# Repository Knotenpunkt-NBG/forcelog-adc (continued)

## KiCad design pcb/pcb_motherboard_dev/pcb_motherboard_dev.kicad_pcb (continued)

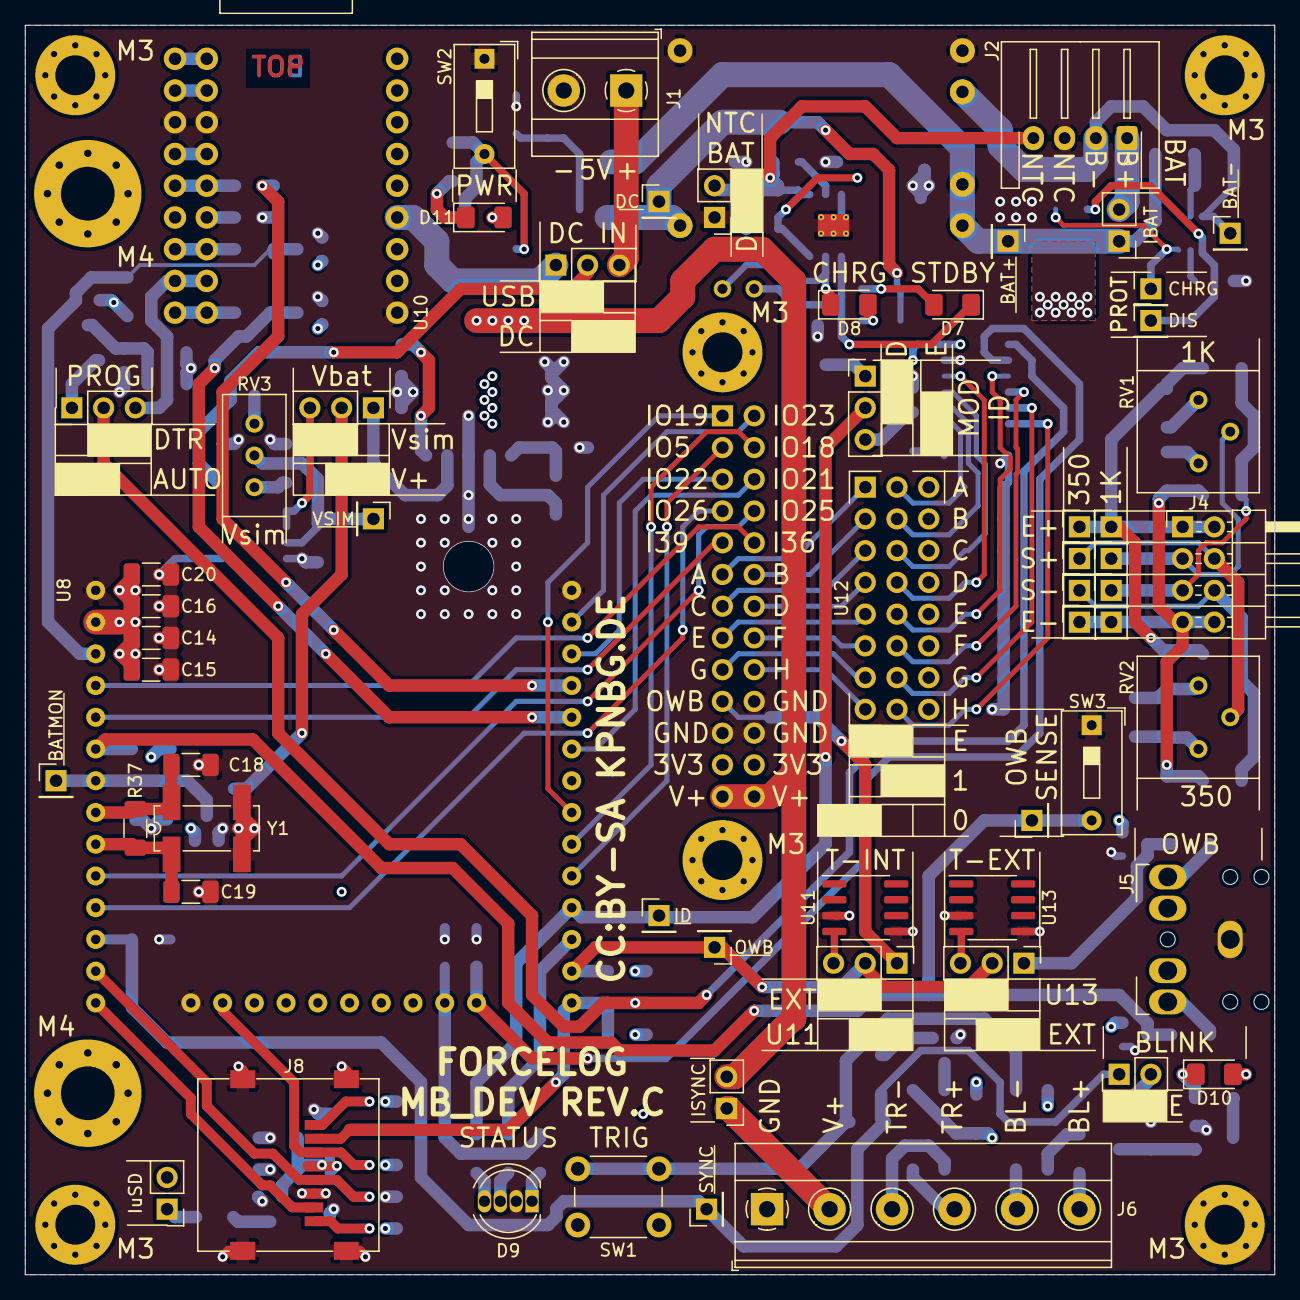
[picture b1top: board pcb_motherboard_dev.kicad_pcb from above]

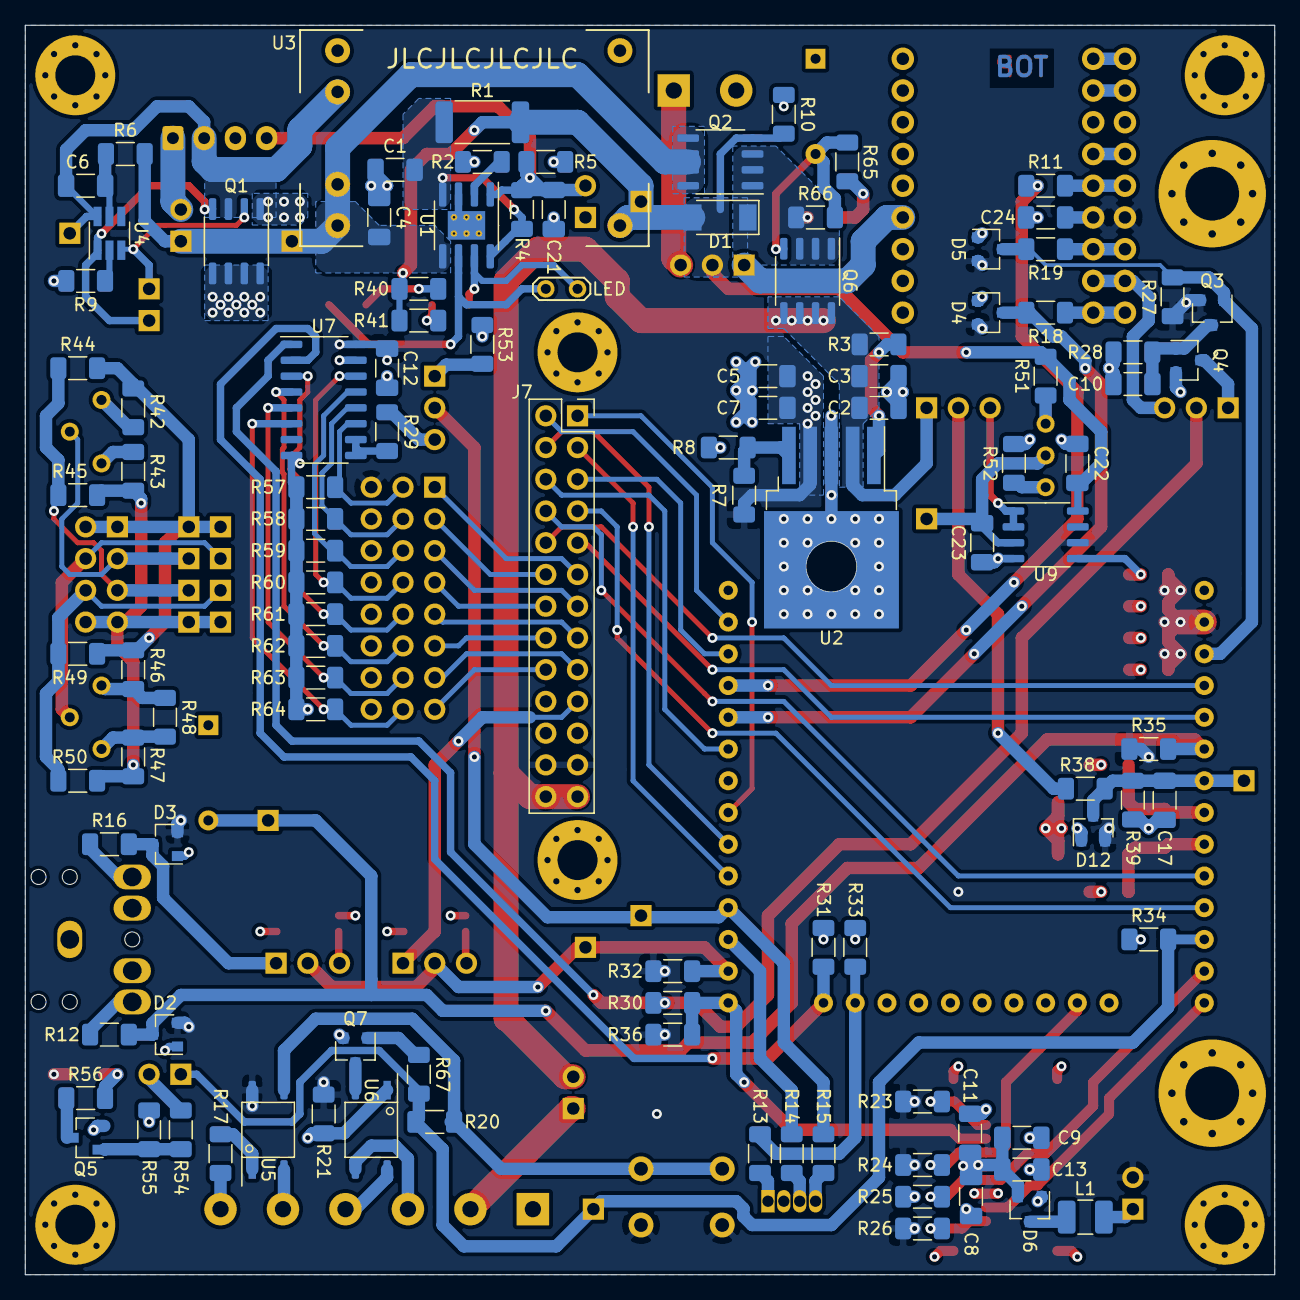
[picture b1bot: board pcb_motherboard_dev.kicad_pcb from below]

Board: 4 copper layers, 100.0 x 100.0 mm, 176 parts (108 on the bottom side), 122 nets.

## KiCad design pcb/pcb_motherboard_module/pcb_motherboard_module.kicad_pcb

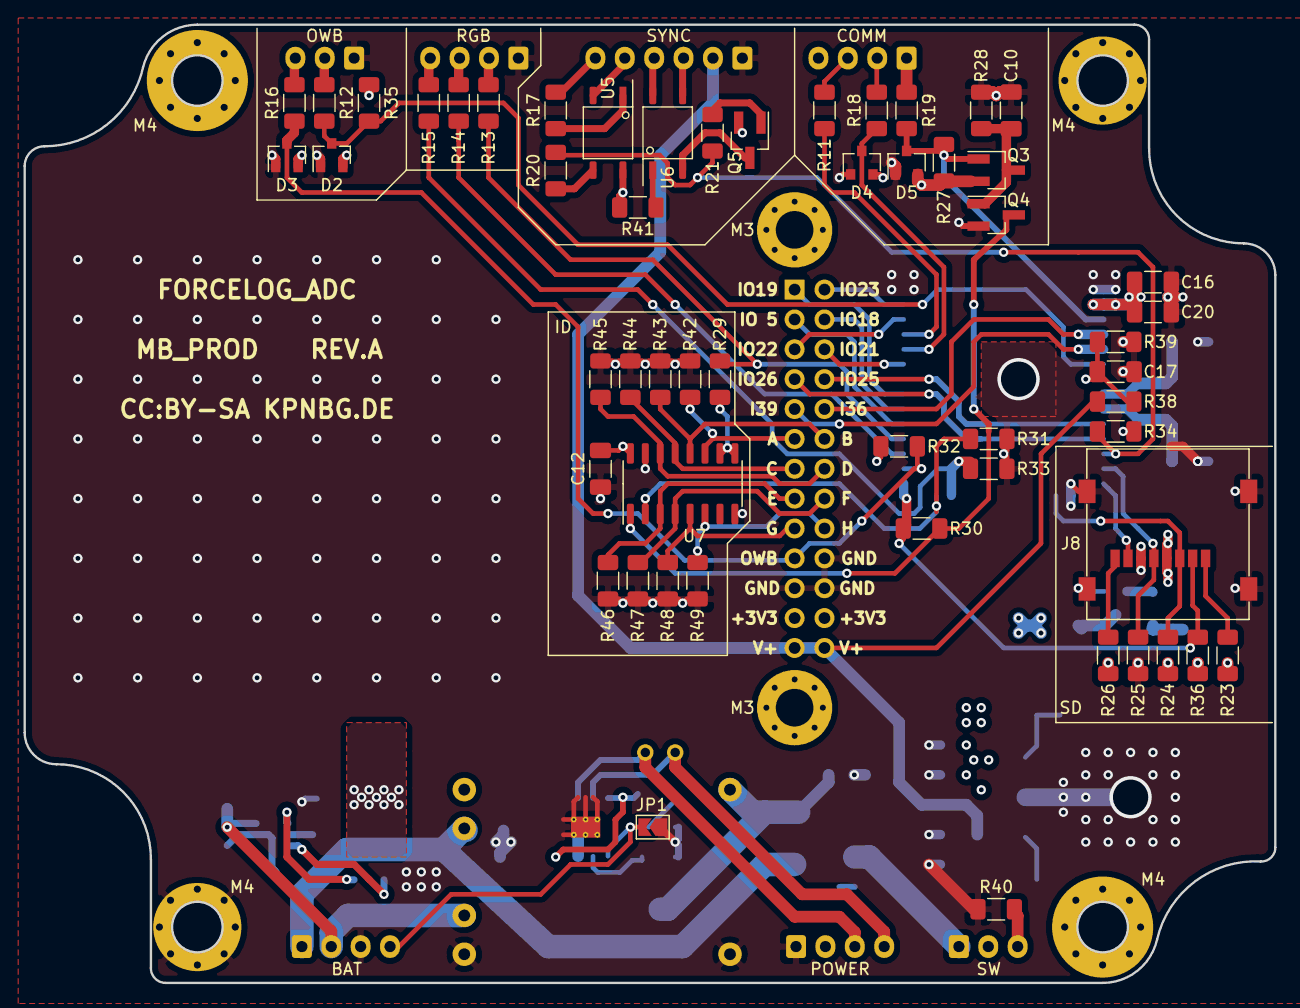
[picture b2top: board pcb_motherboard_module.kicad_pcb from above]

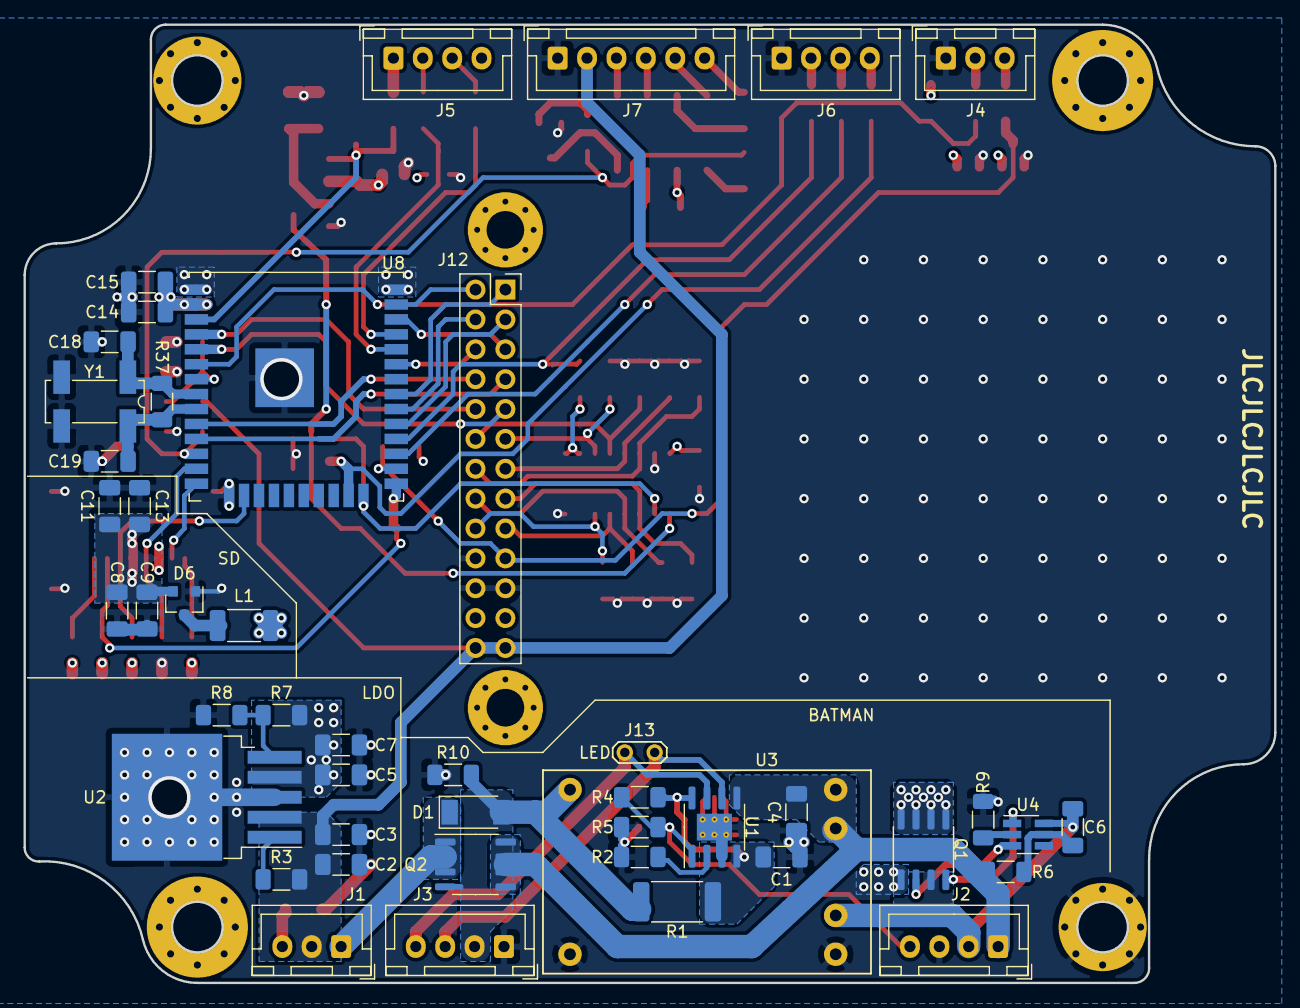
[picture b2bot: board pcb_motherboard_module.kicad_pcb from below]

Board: 4 copper layers, 106.4 x 81.5 mm, 106 parts (46 on the bottom side), 79 nets.

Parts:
C1, C4: 10u; C_1206_3216Metric_Pad1.33x1.80mm_HandSolder
C2, C6, C7, C8, C12, C14, C17: 100n; C_1206_3216Metric_Pad1.33x1.80mm_HandSolder
C3, C5: 22u; C_1206_3216Metric_Pad1.33x1.80mm_HandSolder
C9, C15: 100u; C_1206_3216Metric_Pad1.33x1.80mm_HandSolder
C10: C; C_1206_3216Metric_Pad1.33x1.80mm_HandSolder
C11, C13, C16, C20: 220u; C_1206_3216Metric_Pad1.33x1.80mm_HandSolder
C18, C19: 25p; C_1206_3216Metric_Pad1.33x1.80mm_HandSolder
D1: PMEG3030EP,115; D_SOD-128
D2, D3, D4, D5, D6: BAT54S; SOT-23
H1, H2, H3: MountingHole; MountingHole_4.3mm_M4_Pad_Via
H4: MountingHole_Pad; MountingHole_4.3mm_M4_Pad_Via
H5, H6: MountingHole_Pad; MountingHole_3.2mm_M3_Pad_Via
J1: SW; JST_XH_B3B-XH-A_1x03_P2.50mm_Vertical
J2: BAT; JST_XH_B4B-XH-A_1x04_P2.50mm_Vertical
J3: POWER; JST_XH_B4B-XH-A_1x04_P2.50mm_Vertical
J4: OWB; JST_XH_B3B-XH-A_1x03_P2.50mm_Vertical
J5: COMM; JST_XH_B4B-XH-A_1x04_P2.50mm_Vertical
J6: RGB; JST_XH_B4B-XH-A_1x04_P2.50mm_Vertical
J7: SYNC; JST_XH_B6B-XH-A_1x06_P2.50mm_Vertical
J8: Micro_SD_Card; uSD_Molex_0472192001
J12: Conn_02x13_Odd_Even; PinSocket_2x13_P2.54mm_Vertical
J13: LED; TestPoint_2Pads_Pitch2.54mm_Drill0.8mm
JP1: Jumper_2_Open; SolderJumper-2_P1.3mm_Open_TrianglePad1.0x1.5mm
L1: 47n; L_2010_5025Metric
Q1: DMG9926USD; SO-8_3.9x4.9mm_P1.27mm
Q2: IRF7410TRPBF; SO8_3.8x4.8_SSSGDDDD
Q3: IRLML2244TRPBF; SOT-23_Handsoldering
Q4, Q5: BSS806NE; SOT-23_Handsoldering
R1: 400m; R_2512_6332Metric_Pad1.40x3.35mm_HandSolder
R2: 1k2; R_1206_3216Metric_Pad1.30x1.75mm_HandSolder
R3, R10, R27, R29, R31, R35, R36, R42, R43, R44, R45, R46, R47, R48, R49: 10k; R_1206_3216Metric_Pad1.30x1.75mm_HandSolder
R4, R5, R28, R40: R; R_1206_3216Metric_Pad1.30x1.75mm_HandSolder
R6: 470; R_1206_3216Metric_Pad1.30x1.75mm_HandSolder
R7: 24k; R_1206_3216Metric_Pad1.30x1.75mm_HandSolder
R8: 5k6; R_1206_3216Metric_Pad1.30x1.75mm_HandSolder
R9, R13, R14, R15, R20, R21, R30, R32: 1k; R_1206_3216Metric_Pad1.30x1.75mm_HandSolder
R11, R41: 100; R_1206_3216Metric_Pad1.30x1.75mm_HandSolder
R12, R16, R18, R19: 10; R_1206_3216Metric_Pad1.30x1.75mm_HandSolder
R17: 210; R_1206_3216Metric_Pad1.30x1.75mm_HandSolder
R23, R24, R25, R26, R34: 22k; R_1206_3216Metric_Pad1.30x1.75mm_HandSolder
R33: 100k; R_1206_3216Metric_Pad1.30x1.75mm_HandSolder
R37: 5Meg; R_1206_3216Metric_Pad1.30x1.75mm_HandSolder
R38: 3k; R_1206_3216Metric_Pad1.30x1.75mm_HandSolder
R39: 7k5; R_1206_3216Metric_Pad1.30x1.75mm_HandSolder
U1: TP4056; SOIC-8-1EP_3.9x4.9mm_P1.27mm_EP2.29x3mm_ThermalVias
U2: LP38501; TO-263-5_TabPin6
U3: TP4056withprotect; TP4056_module_prot
U4: NT1713C; SOT-23-6_Handsoldering
U5, U6: EL357NC; EL357N
U7: 74165; SO-16_3.9x9.9mm_P1.27mm
U8: ESP32-WROOM-32; ESP32-WROOM-32U
Y1: 32.768 kHz; Crystal_SMD_SeikoEpson_MC306-4Pin_8.0x3.2mm_HandSoldering

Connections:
+3V3: C5.1, C7.1, C12.1, C14.1, C15.1, C16.1, C20.1, D2.2, D3.2, D4.2, D5.2, J5.4, J12.23, J12.24, L1.2, Q3.2, R7.1, R23.1, R24.1, R26.1, R27.1, R32.1, R35.1, R36.2, R41.2, U2.4, U5.4, U7.16, U8.2
/CONTROLLER/A: J12.11, R42.2, U7.11
/CONTROLLER/B: J12.12, R43.2, U7.12
/CONTROLLER/BLUE: R13.2, R29.2, U8.28
/CONTROLLER/C: J12.13, R44.2, U7.13
/CONTROLLER/CLK: R31.2, U7.2, U8.24
/CONTROLLER/D: J12.14, R45.2, U7.14
/CONTROLLER/DQ: D3.3, J12.19, R16.2, R32.2, U8.26
/CONTROLLER/DTR: Q4.3, R30.2, U7.1
/CONTROLLER/E: J12.15, R46.2, U7.3
/CONTROLLER/F: J12.16, R47.2, U7.4
/CONTROLLER/G: J12.17, R48.2, U7.5
/CONTROLLER/GREEN: R14.2, U8.27
/CONTROLLER/H: J12.18, R49.2, U7.6
/CONTROLLER/HCLK: J8.5, R25.2, U8.13
/CONTROLLER/HMISO: J8.7, U8.14
/CONTROLLER/HMOSI: J8.3, R24.2, U8.16
/CONTROLLER/HMSS: J8.2, R30.1, R36.1, U8.25
/CONTROLLER/IO_5|V~CS: J12.3, U8.29
/CONTROLLER/IO_18|VCLK: J12.4, U8.30
/CONTROLLER/IO_19|VMISO: J12.1, U8.31
/CONTROLLER/IO_21|SDA: J12.6, U8.33
/CONTROLLER/IO_22|SCL: J12.5, U8.36
/CONTROLLER/IO_23|VMOSI: J12.2, U8.37
/CONTROLLER/IO_25|DAC1: J12.8, U8.10
/CONTROLLER/IO_26|DAC2: J12.7, U8.11
/CONTROLLER/I_36|ADC1_0: J12.10, U8.4
/CONTROLLER/I_39|ADC1_3: J12.9, U8.5
/CONTROLLER/OWB_SENSE: D2.3, R12.2, R35.2, U8.6
/CONTROLLER/RED: R15.2, R33.2, U8.23
/CONTROLLER/RTS: D5.3, Q3.1, R19.2, R27.2, U8.3
/CONTROLLER/RXD: D4.3, R18.2, U8.34
/CONTROLLER/SYNC: R20.1, R21.2, R34.2, U8.12
/CONTROLLER/TXD: R11.2, U8.35
/POWER/BAT+: C4.1, J2.1, Q2.1, R6.2, U1.5, U3.5, U3.6
/POWER/BAT-: C6.2, J2.2, Q1.3, U3.4, U4.6
/POWER/DC_IN: D1.2, J3.2, Q2.2, R1.1, R10.1, U3.1
/POWER/SW: D1.1, J1.1, Q2.3
/POWER/TEMP: J2.4, JP1.2, R4.2, R5.1, U1.1
/POWER/~LED_CHRG: J3.4, J13.1, U1.7
/POWER/~LED_STBY: J3.3, J13.2, U1.6
GND: C1.2, C2.2, C3.2, C4.2, C5.2, C7.2, C8.2, C9.2, C10.2, C11.2, C12.2, C13.2, C14.2, C15.2, C16.2, C17.2, C18.1, C19.2, C20.2, D2.1, D3.1, D4.1, D5.1, D6.1, H4.1, J2.3, J3.1, J4.1, J6.1, J7.1, J8.6, J8.9, J12.20, J12.21, J12.22, JP1.1, Q1.1, Q4.2, Q5.2, R2.2, R5.2, R8.2, R9.2, R10.2, R25.1, R28.2, R31.1, R33.1, R34.1, R39.2, R40.2, R42.1, R43.1, R44.1, R45.1, R46.1, R47.1, R48.1, R49.1, U1.3, U1.9, U2.3, U2.6, U3.2, U3.3, U7.8, U7.15, U8.1, U8.15, U8.38, U8.39, Y1.2, Y1.3
unnamed: C1.1, R1.2, R4.1, U1.4, U1.8
unnamed: C6.1, R6.1, U4.5
unnamed: C10.1, Q3.3, Q4.1, R28.1
unnamed: C8.1, C9.1, C11.1, C13.1, D6.2, J8.4
unnamed: C17.1, R38.2, R39.1, U8.7
unnamed: C18.2, R37.2, U8.8, Y1.1
unnamed: C19.1, R37.1, U8.9, Y1.4
unnamed: D6.3, L1.1
unnamed: J1.3, R40.1
unnamed: J4.2, R12.1
unnamed: J4.3, R16.1
unnamed: J5.1, R19.1
unnamed: J5.2, R18.1
unnamed: J5.3, R11.1
unnamed: J6.2, R13.1
unnamed: J6.3, R14.1
unnamed: J6.4, R15.1
unnamed: J7.3, U6.3
unnamed: J7.4, U6.4
unnamed: J7.5, U5.2
unnamed: J7.6, R17.1
unnamed: J8.1, R23.2
unnamed: J8.8, R26.2
unnamed: Q1.2, U4.3
unnamed: Q1.4, U4.1
unnamed: Q1.5, Q1.6, Q1.7, Q1.8
unnamed: Q5.1, R21.1
unnamed: Q5.3, U6.2
unnamed: R2.1, U1.2
unnamed: R3.1, U2.1
unnamed: R7.2, R8.1, U2.5
unnamed: R9.1, U4.2
unnamed: R17.2, U5.1
unnamed: R20.2, U5.3
unnamed: R29.1, U7.9, U7.10
unnamed: R41.1, U6.1
VDD: C2.1, C3.1, J1.2, J7.2, J12.25, J12.26, R3.2, R38.1, U2.2

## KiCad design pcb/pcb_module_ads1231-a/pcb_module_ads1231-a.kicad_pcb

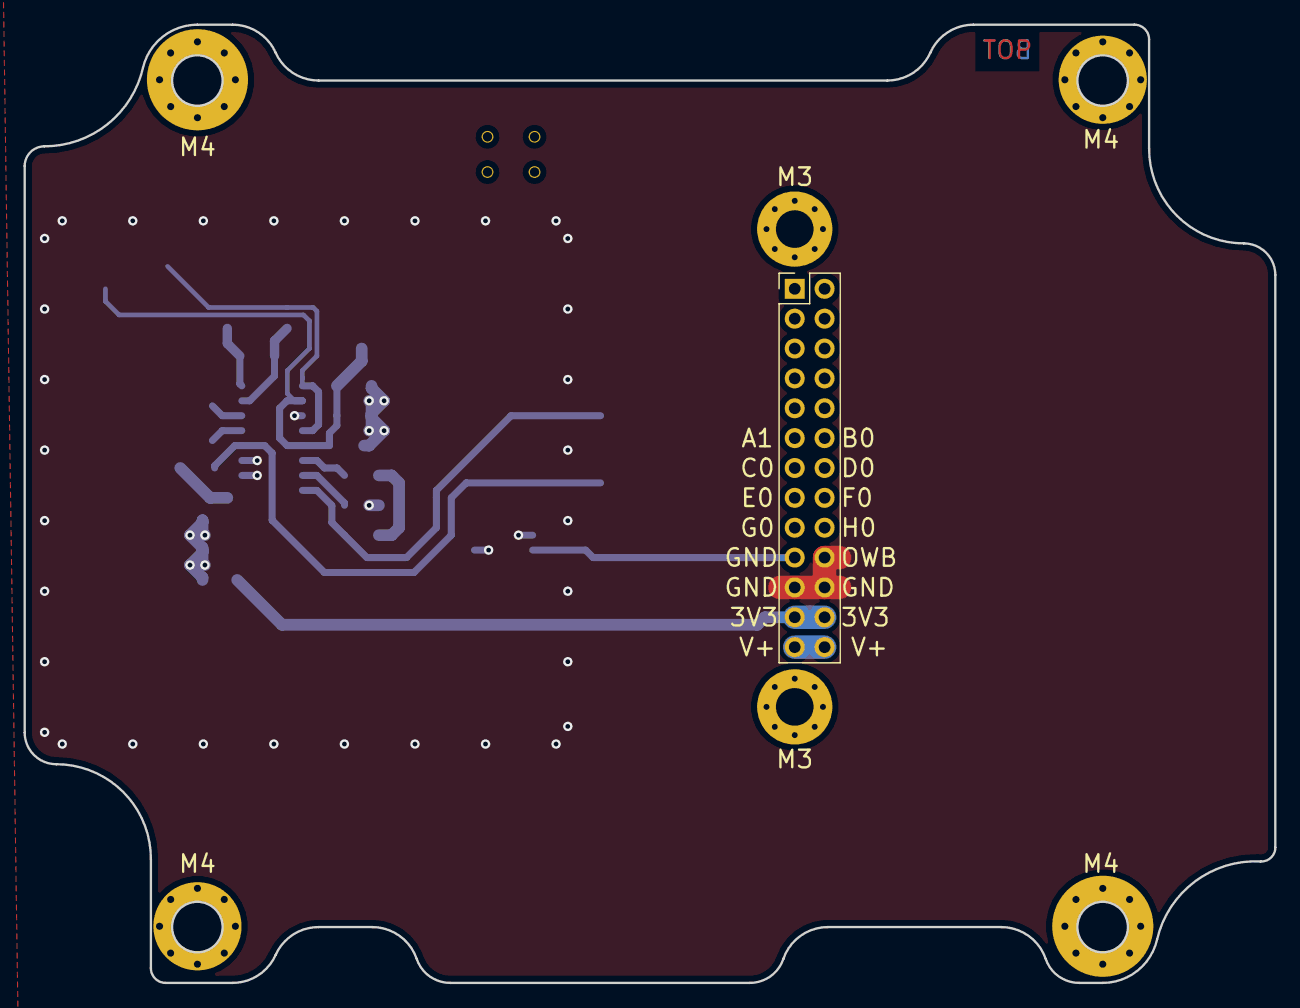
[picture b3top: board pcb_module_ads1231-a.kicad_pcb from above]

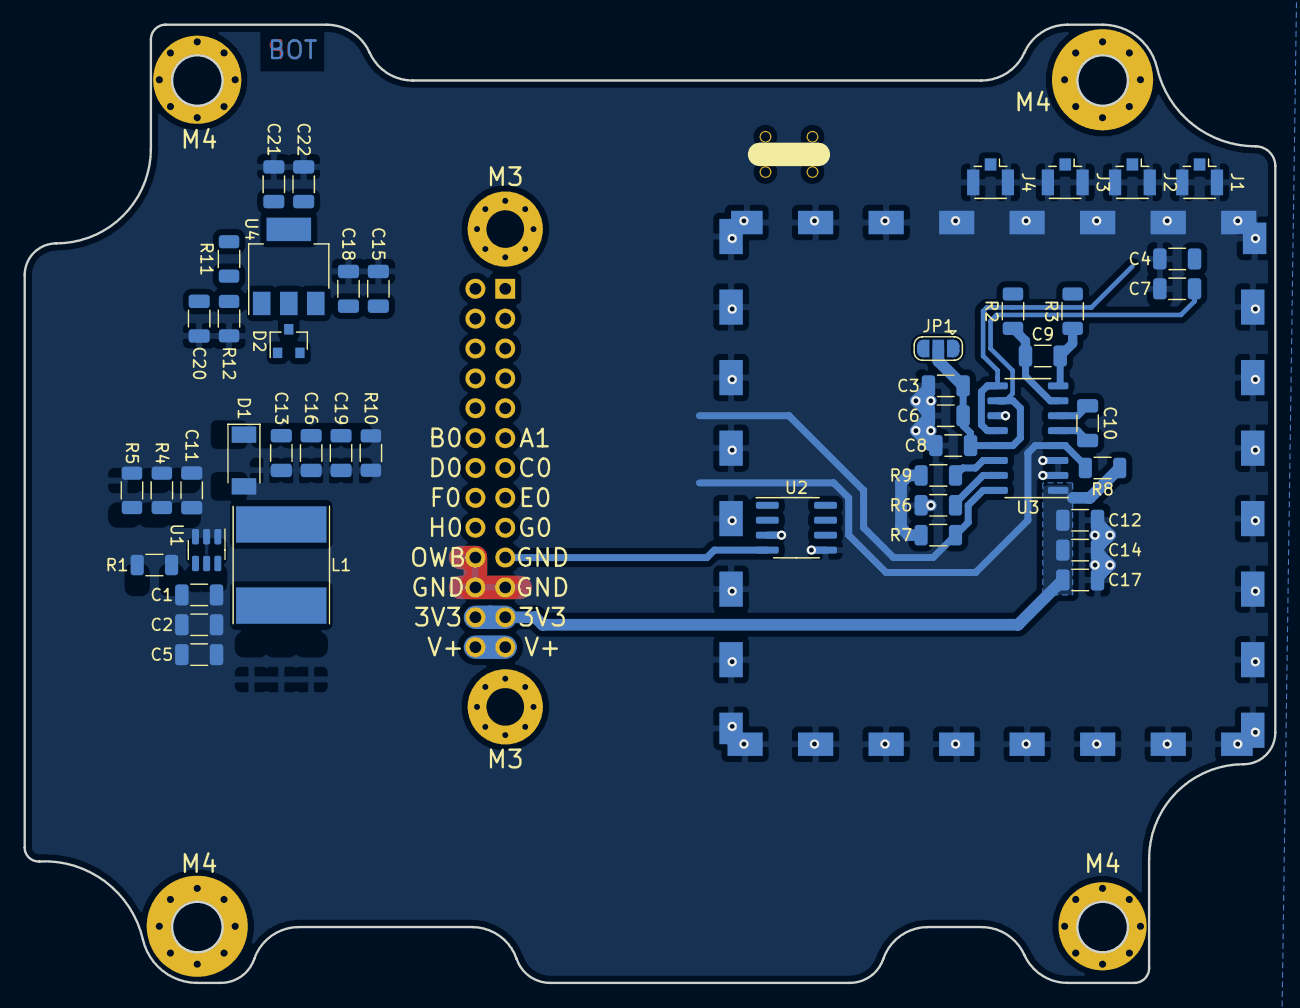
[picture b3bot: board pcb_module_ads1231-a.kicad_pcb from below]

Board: 2 copper layers, 106.4 x 81.5 mm, 55 parts (48 on the bottom side), 22 nets.

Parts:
C1, C4, C8, C9, C10, C12, C13, C18, C21: 100n; C_1206_3216Metric
C2, C6, C7, C14, C15, C16, C22: 10u; C_1206_3216Metric
C3, C17: 47u; C_1206_3216Metric
C5, C19: 100u; C_1206_3216Metric
C11: 330p; C_1206_3216Metric
C20: 10n; C_1206_3216Metric
D1: PMEG3030EP,115; D_SOD-128
D2: D_Dual_Series_AKC; SOT-23
H1, H2: MountingHole_Pad; MountingHole_3.2mm_M3_Pad_Via
H3: MountingHole; cableclamp_4x1.13_coax_bundled
H4, H5, H6, H7: MountingHole_Pad; MountingHole_4.3mm_M4_Pad_Via
J1, J2, J3, J4: Conn_Coaxial; U.FL_Hirose_U.FL-R-SMT-1_Vertical
J5: RFShield_TwoPieces; Shield_TE2118726-2
J7: Conn_02x13_Odd_Even; PinHeader_2x13_P2.54mm_Vertical
JP1: SolderJumper_3_Open; SolderJumper-3_P1.3mm_Open_RoundedPad1.0x1.5mm
L1: 10u; L_Taiyo-Yuden_NR-80xx_HandSoldering
R1: 51k; R_1206_3216Metric
R2, R3: 100; R_1206_3216Metric
R4: 130k; R_1206_3216Metric
R5: 9k1; R_1206_3216Metric
R6, R7, R8, R9: 10k; R_1206_3216Metric
R10, R12: 1k; R_1206_3216Metric
R11: 330; R_1206_3216Metric
U1: MT3608; SOT-23-6
U2: DS18B20Z; SOIC-8_3.9x4.9mm_P1.27mm
U3: ads1231; SO-16_3.9x9.9mm_P1.27mm
U4: LM317_SOT-223; SOT-223-3_TabPin2

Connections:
+3V3: C12.1, C14.1, C17.1, J7.23, J7.24, JP1.3, R7.1, R8.1, R9.1, U3.1
+5VA: C21.1, C22.1, D2.3, JP1.1, R11.1, U4.2
+9V: C11.1, C13.1, C15.1, C16.1, C18.1, C19.1, D1.1, D2.2, R4.1, R10.1, U4.3
/DOUT: J7.1, R7.2, U3.16
/DQ: J7.19, U2.4
/E+: C3.1, C4.1, C6.1, C7.1, C8.1, J1.1, JP1.2, U3.10, U3.13
/E-: J2.1, U3.9, U3.12
/EN: R1.2, U1.4
/PDWN: J7.8, R9.2, U3.14
/S+: J4.1, R2.2
/S-: J3.1, R3.2
/SCLK: J7.4, R6.2, U3.15
/SPEED: J7.6, R8.2, U3.4
GND: C1.2, C2.2, C3.2, C4.2, C5.2, C6.2, C7.2, C8.2, C12.2, C13.2, C14.2, C15.2, C16.2, C17.2, C18.2, C19.2, C20.2, C21.2, C22.2, J1.2, J2.2, J3.2, J4.2, J5.1, J7.20, J7.21, J7.22, R5.2, R6.1, R10.2, R12.2, U1.2, U2.3, U2.5, U3.2, U3.3, U3.11
unnamed: C9.1, R2.1, U3.7
unnamed: C9.2, R3.1, U3.8
unnamed: C10.1, U3.5
unnamed: C10.2, U3.6
unnamed: C11.2, R4.2, R5.1, U1.3
unnamed: C20.1, D2.1, R11.2, R12.1, U4.1
unnamed: D1.2, L1.2, U1.1
V+: C1.1, C2.1, C5.1, J7.25, J7.26, L1.1, R1.1, U1.5

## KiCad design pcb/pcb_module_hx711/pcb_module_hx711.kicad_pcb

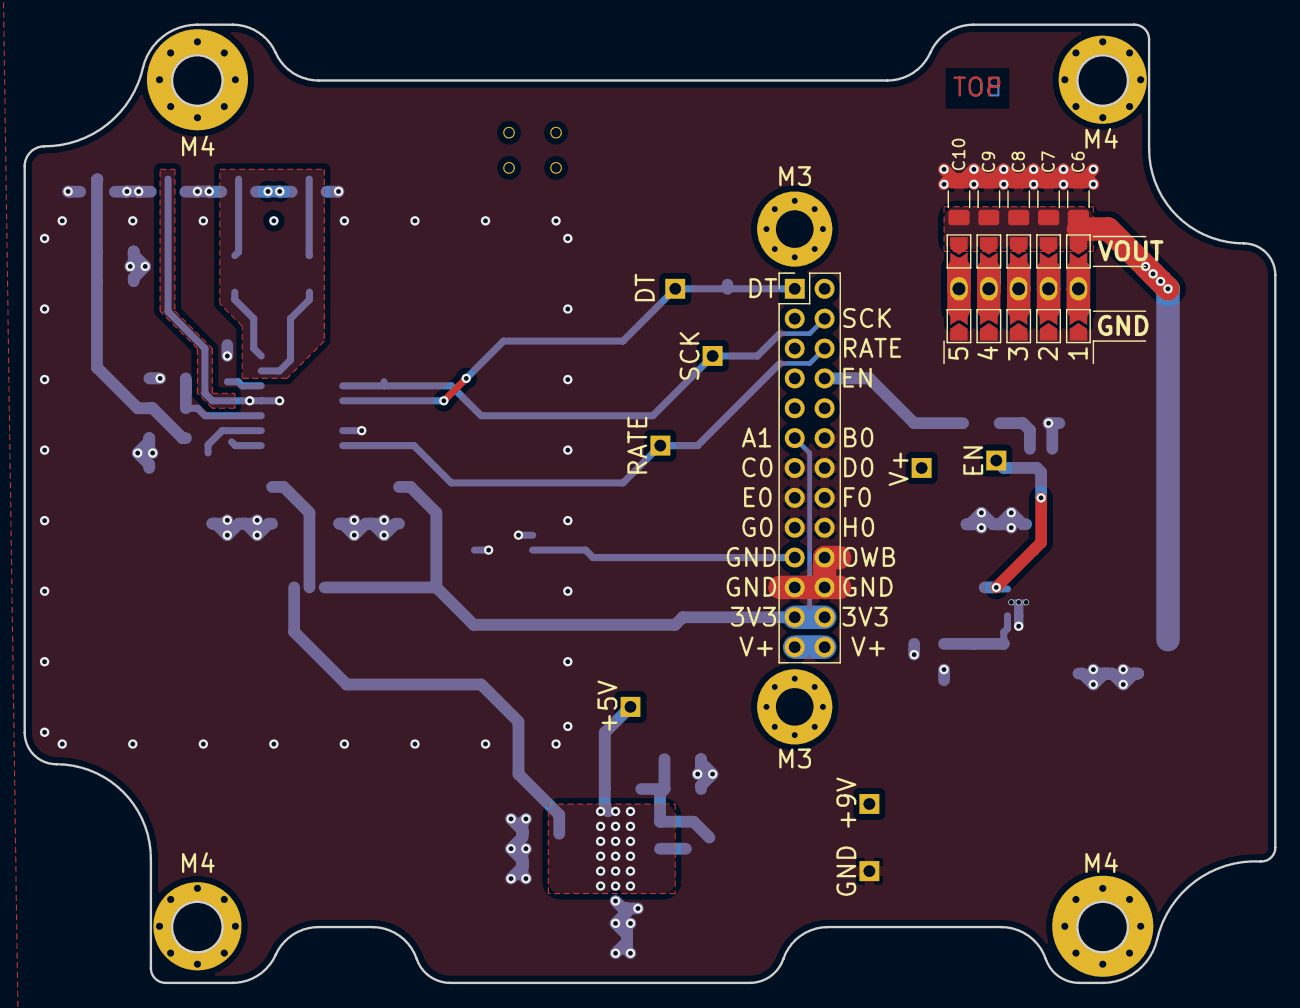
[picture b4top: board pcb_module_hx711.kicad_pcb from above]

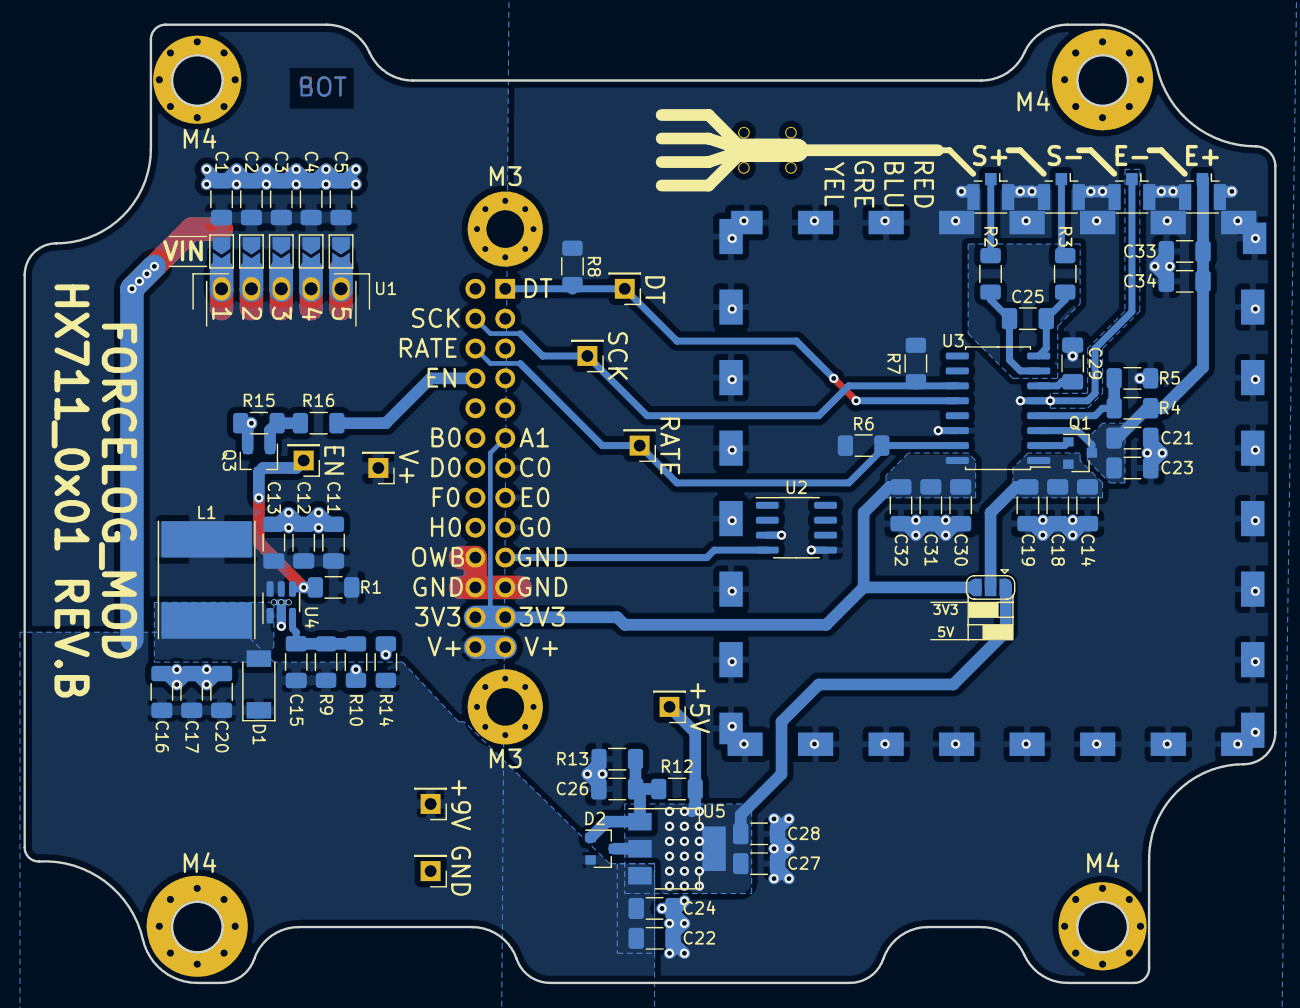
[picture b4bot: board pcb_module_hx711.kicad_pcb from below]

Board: 2 copper layers, 106.4 x 81.5 mm, 96 parts (74 on the bottom side), 29 nets.

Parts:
C1, C2, C3, C4, C5, C6, C7, C8, C9, C10, C12, C17, C18, C22, C23, C26, C28, C31, C34: 10u; C_1206_3216Metric_Pad1.33x1.80mm_HandSolder
C11, C16: 100u; C_1206_3216Metric_Pad1.33x1.80mm_HandSolder
C13, C19, C20, C21, C24, C25, C27, C29, C30, C33: 100n; C_1206_3216Metric_Pad1.33x1.80mm_HandSolder
C14, C32: 47u; C_1206_3216Metric_Pad1.33x1.80mm_HandSolder
C15: 330p; C_1206_3216Metric_Pad1.33x1.80mm_HandSolder
D1: D_Schottky; D_SOD-128
D2: BAT54S; SOT-23
H1, H2: MountingHole_Pad; MountingHole_3.2mm_M3_Pad_Via
H3: MountingHole; cableclamp_4x1.13_coax_bundled
H4, H5, H6, H7: MountingHole_Pad; MountingHole_4.3mm_M4_Pad_Via
J1: E+; U.FL_Hirose_U.FL-R-SMT-1_Vertical
J2: E-; U.FL_Hirose_U.FL-R-SMT-1_Vertical
J3: S+; U.FL_Hirose_U.FL-R-SMT-1_Vertical
J4: S-; U.FL_Hirose_U.FL-R-SMT-1_Vertical
J5: RFShield_TwoPieces; Shield_TE2118726-2
J7: Conn_02x13_Odd_Even; PinHeader_2x13_P2.54mm_Vertical
JP1, JP2, JP3, JP4, JP5, JP6, JP7, JP8, JP9, JP10, JP11, JP12, JP13, JP14, JP15: Jumper_2_Open; SolderJumper-2_P1.3mm_Open_TrianglePad1.0x1.5mm
JP16: Jumper_3_Open; SolderJumper-3_P1.3mm_Open_RoundedPad1.0x1.5mm
L1: 10; L_Taiyo-Yuden_NR-80xx_HandSoldering
Q1: MMBT4403L; SOT-23
Q3: BSS806NE; SOT-23
R1: 51k; R_1206_3216Metric_Pad1.30x1.75mm_HandSolder
R2, R3: 100; R_1206_3216Metric_Pad1.30x1.75mm_HandSolder
R4: 20k; R_1206_3216Metric_Pad1.30x1.75mm_HandSolder
R5: 7k15; R_1206_3216Metric_Pad1.30x1.75mm_HandSolder
R6, R7, R8, R15: 10k; R_1206_3216Metric_Pad1.30x1.75mm_HandSolder
R9: 130k; R_1206_3216Metric_Pad1.30x1.75mm_HandSolder
R10: 9k1; R_1206_3216Metric_Pad1.30x1.75mm_HandSolder
R12: 330; R_1206_3216Metric_Pad1.30x1.75mm_HandSolder
R13, R14: 1k; R_1206_3216Metric_Pad1.30x1.75mm_HandSolder
R16: 220; R_1206_3216Metric_Pad1.30x1.75mm_HandSolder
TP1, TP2: GND; PinHeader_1x01_P2.54mm_Vertical
TP3: SCK; PinHeader_1x01_P2.54mm_Vertical
TP4: DT; PinHeader_1x01_P2.54mm_Vertical
TP5: RATE; PinHeader_1x01_P2.54mm_Vertical
TP6: +9V; PinHeader_1x01_P2.54mm_Vertical
TP7: +5V; PinHeader_1x01_P2.54mm_Vertical
TP8: TP; PinHeader_1x01_P2.54mm_Vertical
U1: BOOST MODULE; boost_generic_var
U2: DS18B20Z; SOIC-8_3.9x4.9mm_P1.27mm
U3: HX711; SO-16_5.3x10.2mm_P1.27mm
U4: MT3608; SOT-23-6
U5: LM317_SOT-223; SOT-223-3_TabPin2

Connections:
+3V3: C30.1, C31.1, C32.1, J7.11, J7.23, J7.24, JP16.3, U3.16
+5VA: C27.1, C28.1, D2.3, JP16.1, R12.1, TP7.1, U5.2
+9V: C6.2, C7.2, C8.2, C9.2, C10.2, C15.1, C16.1, C17.1, C20.1, C22.1, C24.1, D1.1, D2.2, JP11.1, JP12.1, JP13.1, JP14.1, JP15.1, R9.1, R14.1, TP6.1, U5.3
/BOOST_PIN1: JP1.2, JP6.2, JP11.2, U1.1
/BOOST_PIN2: JP2.2, JP7.2, JP12.2, U1.2
/BOOST_PIN3: JP3.2, JP8.2, JP13.2, U1.3
/BOOST_PIN4: JP4.2, JP9.2, JP14.2, U1.4
/BOOST_PIN5: JP5.2, JP10.2, JP15.2, U1.5
/DQ: J7.19, U2.4
/DT: J7.1, R8.2, TP4.1, U3.12
/EN: Q3.3, R1.2, TP8.1, U4.4
/RATE: J7.6, R6.2, TP5.1, U3.15
/SCK: J7.4, R7.2, TP3.1, U3.11
GND: C1.1, C2.1, C3.1, C4.1, C5.1, C6.1, C7.1, C8.1, C9.1, C10.1, C11.2, C12.2, C13.2, C14.2, C16.2, C17.2, C18.2, C19.2, C20.2, C21.2, C22.2, C23.2, C24.2, C26.2, C27.2, C28.2, C29.2, C30.2, C31.2, C32.2, C33.2, C34.2, J1.2, J2.2, J3.2, J4.2, J5.1, J7.12, J7.13, J7.14, J7.15, J7.16, J7.17, J7.18, J7.20, J7.21, J7.22, JP6.1, JP7.1, JP8.1, JP9.1, JP10.1, Q3.2, R5.2, R6.1, R7.1, R8.1, R10.2, R13.2, R14.2, R15.2, TP2.1, U2.3, U2.5, U3.5, U3.14, U4.2
unnamed: C14.1, C18.1, C19.1, JP16.2, Q1.2, U3.1
unnamed: C15.2, R9.2, R10.1, U4.3
unnamed: C21.1, C23.1, C33.1, C34.1, J1.1, Q1.3, R4.1, U3.3
unnamed: C25.1, R2.2, U3.7
unnamed: C25.2, R3.2, U3.8
unnamed: C26.1, D2.1, R12.2, R13.1, U5.1
unnamed: C29.1, U3.6
unnamed: D1.2, L1.2, U4.1
unnamed: J3.1, R3.1
unnamed: J4.1, R2.1
unnamed: J7.8, R16.2
unnamed: Q1.1, U3.2
unnamed: Q3.1, R15.1, R16.1
unnamed: R4.2, R5.1, U3.4
V+: C1.2, C2.2, C3.2, C4.2, C5.2, C11.1, C12.1, C13.1, J7.25, J7.26, JP1.1, JP2.1, JP3.1, JP4.1, JP5.1, L1.1, R1.1, TP1.1, U4.5, U4.6

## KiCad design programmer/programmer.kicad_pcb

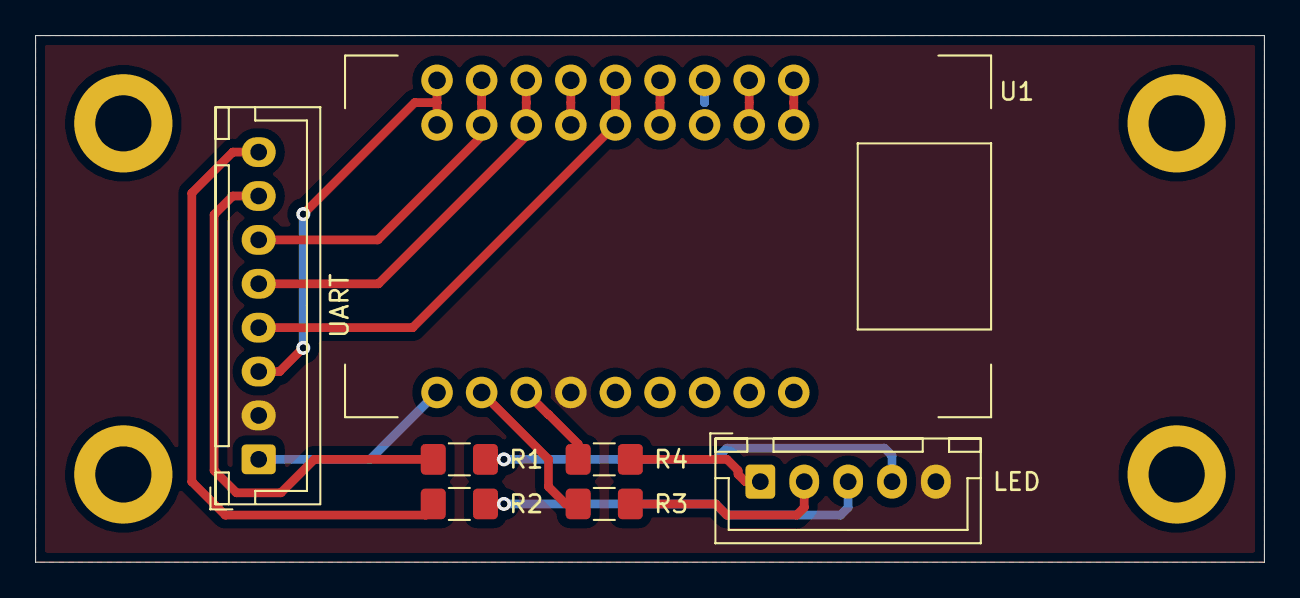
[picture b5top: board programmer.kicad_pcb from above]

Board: 2 copper layers, 70.0 x 30.0 mm, 11 parts (0 on the bottom side), 14 nets.

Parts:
P1: UART; JST_XH_B8B-XH-A_1x08_P2.50mm_Vertical
P2: LED; JST_XH_B5B-XH-A_1x05_P2.50mm_Vertical
P3, P4, P5, P6: CONN_01X01; MountingHole_3.2mm_M3_DIN965_Pad
R1, R2, R3, R4: 150; R_1206_3216Metric_Pad1.42x1.75mm_HandSolder
U1: FT232breakout; ft232rl_breakout_combined

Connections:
+5V: P1.2, P2.5, U1.15
/CHRGLED: P1.7, R1.2
/DTR: P1.6, U1.8
/FINLED: P1.8, R2.2
/RTS: P1.5, U1.7
/RXD: P1.4, U1.5
/RXLED: R4.2, U1.16
/TXD: P1.3, U1.9
/TXLED: R3.2, U1.17
GND: P1.1, U1.3, U1.18
unnamed: P2.1, R4.1
unnamed: P2.2, R3.1
unnamed: P2.3, R2.1
unnamed: P2.4, R1.1

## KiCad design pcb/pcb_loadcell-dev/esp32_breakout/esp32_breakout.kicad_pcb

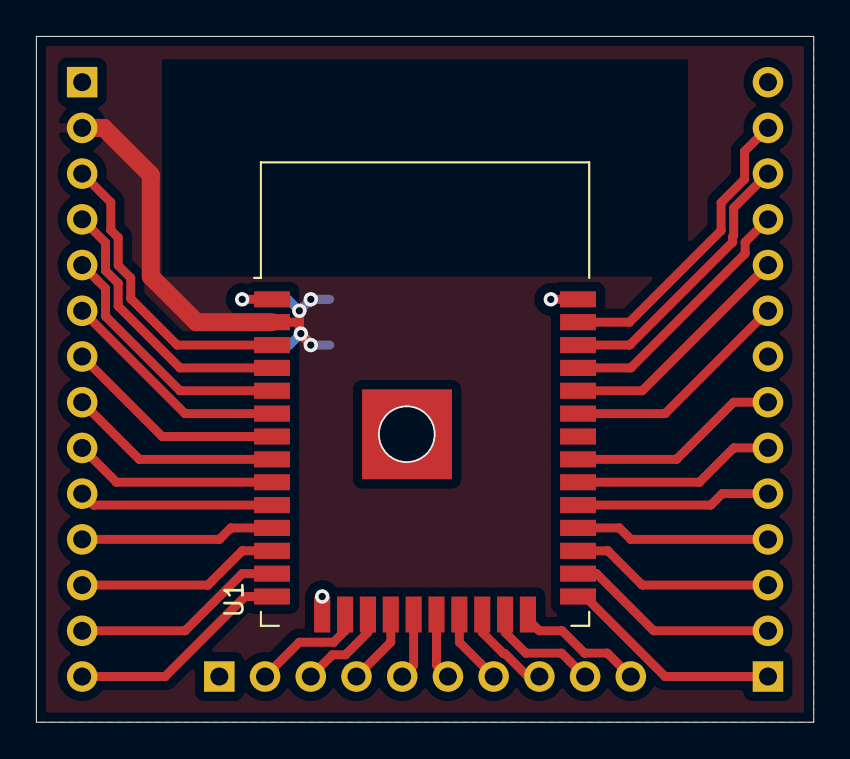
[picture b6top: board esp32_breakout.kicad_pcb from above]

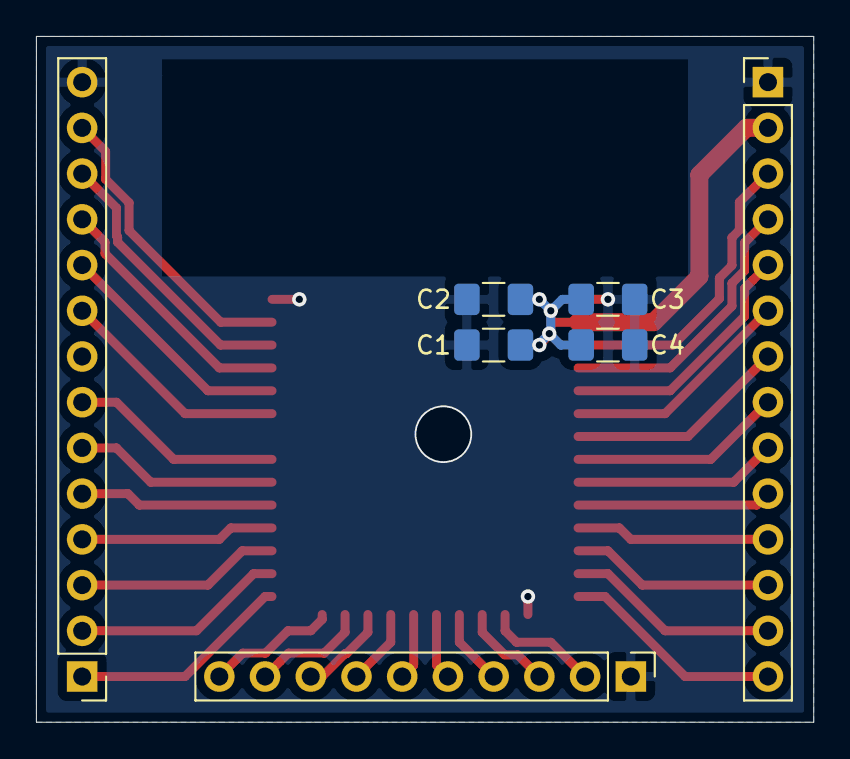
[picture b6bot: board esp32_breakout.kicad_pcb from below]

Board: 2 copper layers, 43.2 x 38.1 mm, 8 parts (7 on the bottom side), 35 nets.

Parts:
C1, C2: 100n; C_1206_3216Metric_Pad1.42x1.75mm_HandSolder
C3, C4: 10µ; C_1206_3216Metric_Pad1.42x1.75mm_HandSolder
P1, P2: CONN_01X14; PinHeader_1x14_P2.54mm_Vertical
P3: CONN_01X10; PinHeader_1x10_P2.54mm_Vertical
U1: ESP32-WROOM-32

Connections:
+3V3: C1.1, C2.1, C3.1, C4.1, P1.2, U1.2
/P1_3: P1.3, U1.3
/P1_4: P1.4, U1.4
/P1_5: P1.5, U1.5
/P1_6: P1.6, U1.6
/P1_7: P1.7, U1.7
/P1_8: P1.8, U1.8
/P1_9: P1.9, U1.9
/P1_10: P1.10, U1.10
/P1_11: P1.11, U1.11
/P1_12: P1.12, U1.12
/P1_13: P1.13, U1.13
/P1_14: P1.14, U1.14
/P2_1: P2.1, U1.25
/P2_2: P2.2, U1.26
/P2_3: P2.3, U1.27
/P2_4: P2.4, U1.28
/P2_5: P2.5, U1.29
/P2_6: P2.6, U1.30
/P2_7: P2.7, U1.31
/P2_9: P2.9, U1.33
/P2_10: P2.10, U1.34
/P2_11: P2.11, U1.35
/P2_12: P2.12, U1.36
/P2_13: P2.13, U1.37
/P3_2: P3.2, U1.16
/P3_3: P3.3, U1.17
/P3_4: P3.4, U1.18
/P3_5: P3.5, U1.19
/P3_6: P3.6, U1.20
/P3_7: P3.7, U1.21
/P3_8: P3.8, U1.22
/P3_9: P3.9, U1.23
/P3_10: P3.10, U1.24
GND: C1.2, C2.2, C3.2, C4.2, P1.1, P2.14, P3.1, U1.1, U1.15, U1.38, U1.39
